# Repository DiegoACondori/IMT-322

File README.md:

# IMT-322/DIEGO/A/CONDORI/CALIZAYA

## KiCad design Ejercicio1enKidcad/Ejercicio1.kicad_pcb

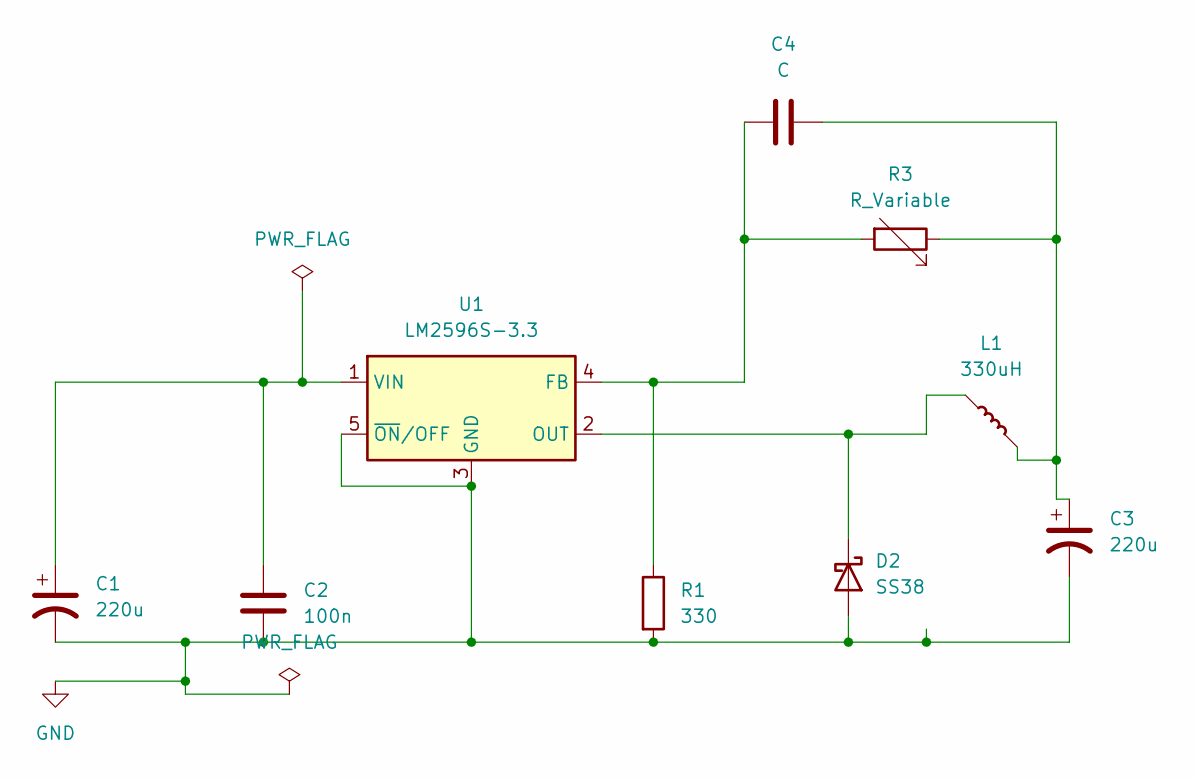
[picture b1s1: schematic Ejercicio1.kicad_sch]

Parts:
C1, C3: 220u; CP_Elec_5x3.9
C2: 100n; C_0504_1310Metric_Pad0.83x1.28mm_HandSolder
C4: C; C_Elec_4x5.8
D2: SS38; D_SMA
L1: 330uH; L_0402_1005Metric
R1: 330; R_0402_1005Metric_Pad0.72x0.64mm_HandSolder
R3: R_Variable; Potentiometer_Bourns_3386W_Horizontal
U1: LM2596S-3.3; TO-263-5_TabPin3

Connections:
GND: C1.2, C2.2, C3.2, D2.2 (A), R1.2, U1.3 (GND), U1.5 (~ON/OFF)
unnamed: C3.1, C4.2, L1.1, R3.1
unnamed: D2.1 (K), L1.2, U1.2 (OUT)
unnamed: C4.1, R1.1, R3.2, U1.4 (FB)
unnamed: C1.1, C2.1, U1.1 (VIN)

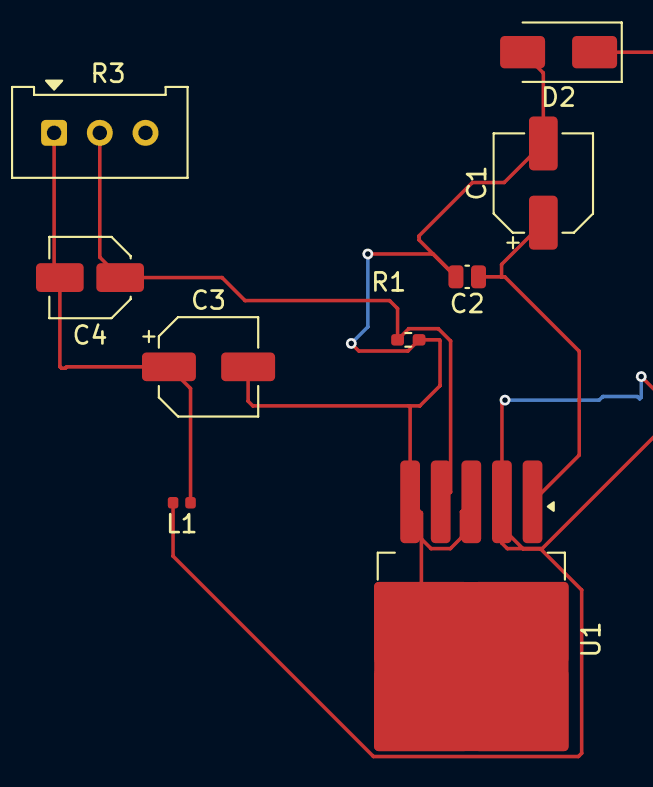
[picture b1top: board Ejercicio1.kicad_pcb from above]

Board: 2 copper layers, 9 parts (0 on the bottom side), 5 nets.

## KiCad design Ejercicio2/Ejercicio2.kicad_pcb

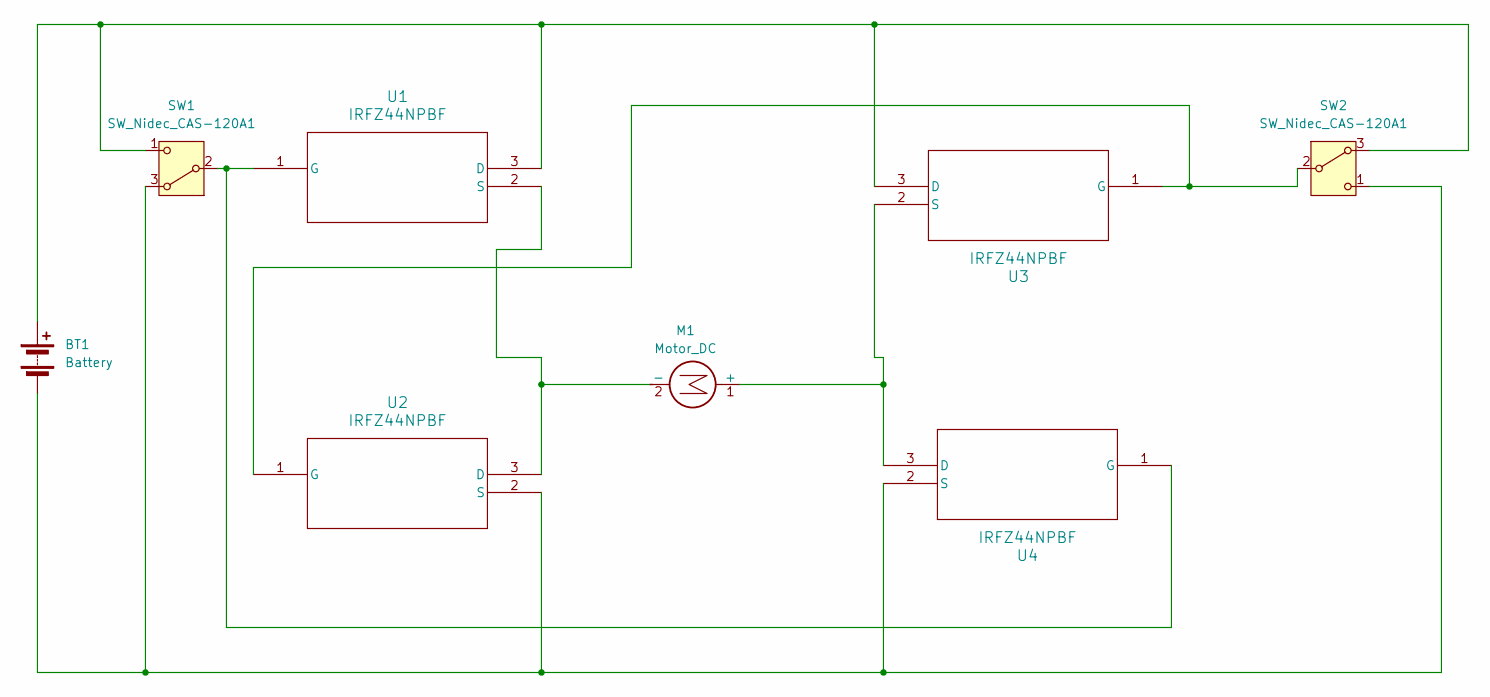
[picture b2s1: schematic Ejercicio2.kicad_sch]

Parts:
BT1: Battery; BatteryHolder_Keystone_1042_1x18650
M1: Motor_DC; PinHeader_1x02_P2.54mm_Vertical
SW1, SW2: SW_Nidec_CAS-120A1; Nidec_Copal_CAS-120A
U1, U2, U3, U4: IRFZ44NPBF; PG-TO220-3_INF

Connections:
unnamed: BT1.1 (+), SW1.1 (C), SW2.3 (A), U1.3 (D), U3.3 (D)
unnamed: BT1.2 (-), SW1.3 (A), SW2.1 (C), U2.2 (S), U4.2 (S)
unnamed: M1.1 (+), U3.2 (S), U4.3 (D)
unnamed: M1.2 (-), U1.2 (S), U2.3 (D)
unnamed: SW1.2 (B), U1.1 (G), U4.1 (G)
unnamed: SW2.2 (B), U2.1 (G), U3.1 (G)

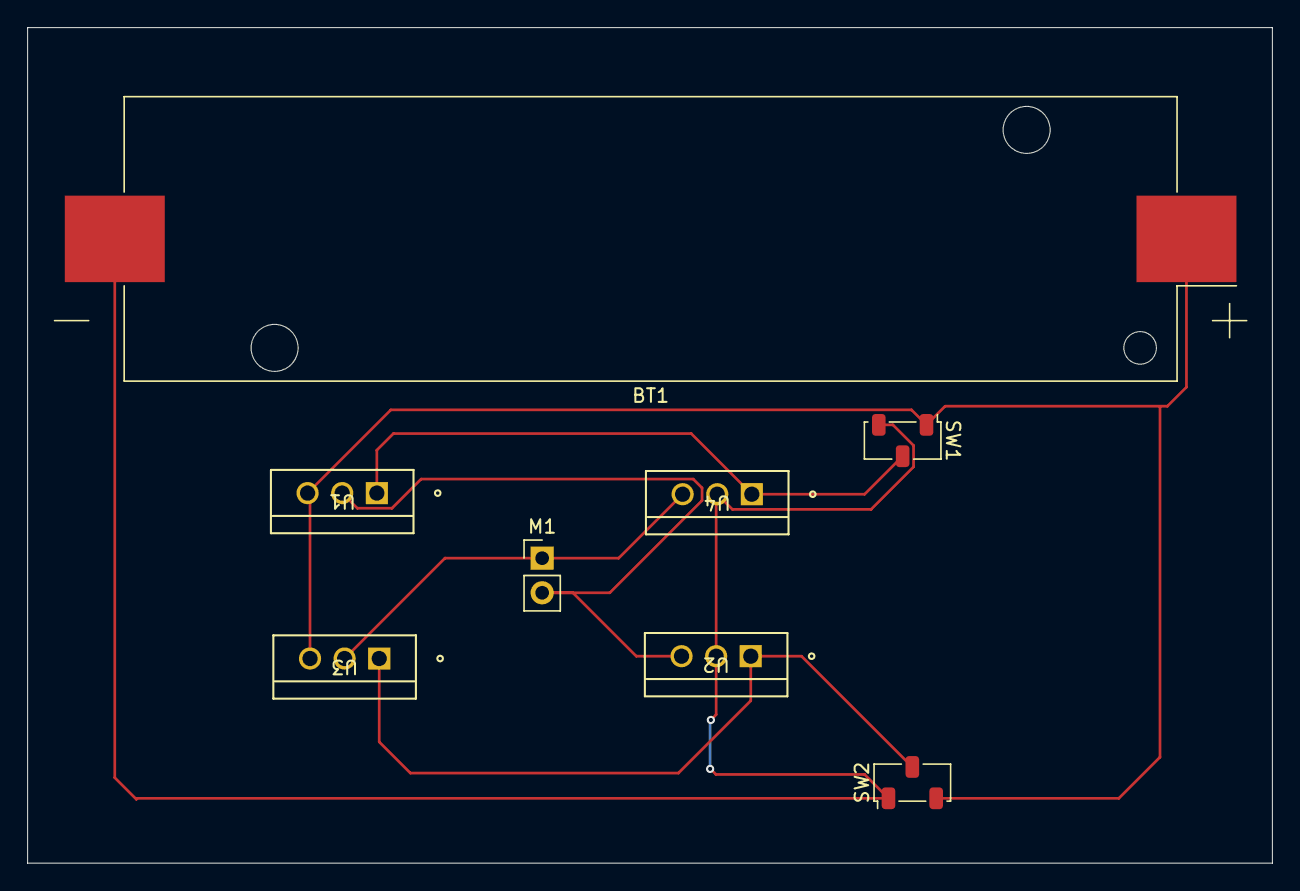
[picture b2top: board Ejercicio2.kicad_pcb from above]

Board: 2 copper layers, 91.4 x 61.3 mm, 8 parts (0 on the bottom side), 6 nets.

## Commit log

2024-02-17 prueba
2024-02-17 Blink
2024-03-19 Ejercicio3
2024-03-19 Actualizacion
2024-03-19 EXAMEN DE LABORATORIO
2024-04-06 kidcad
2024-04-20 Semaforo
2024-04-21 EjercicioConSensorDeProximi
2024-04-23 Acensor de 3 pisos
2024-04-27 EXAMEN2
2024-05-21 BlinkCortexA
2024-05-23 Recuperatorio
2024-06-01 ANIMACION_DEL_COMPRESOR
